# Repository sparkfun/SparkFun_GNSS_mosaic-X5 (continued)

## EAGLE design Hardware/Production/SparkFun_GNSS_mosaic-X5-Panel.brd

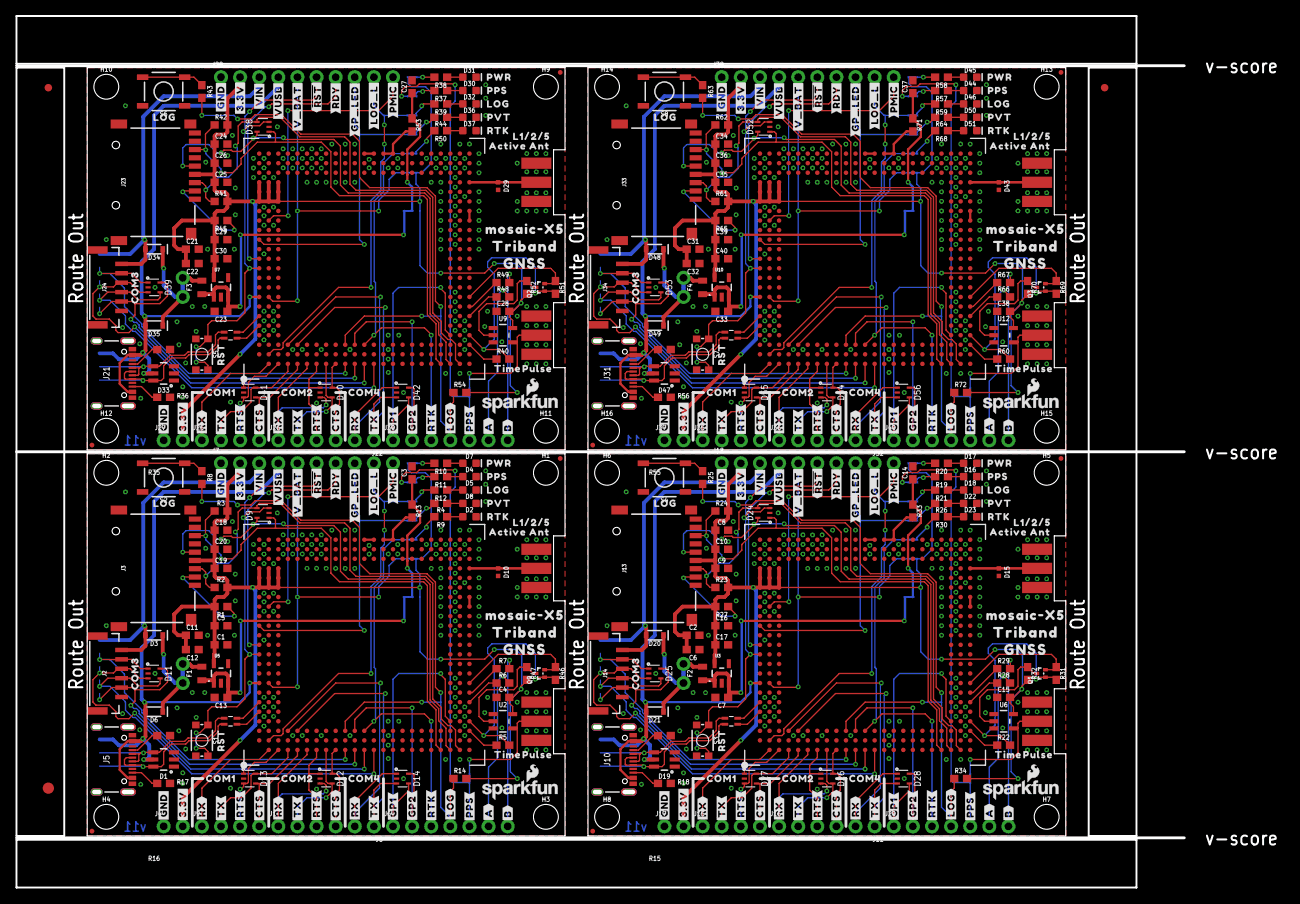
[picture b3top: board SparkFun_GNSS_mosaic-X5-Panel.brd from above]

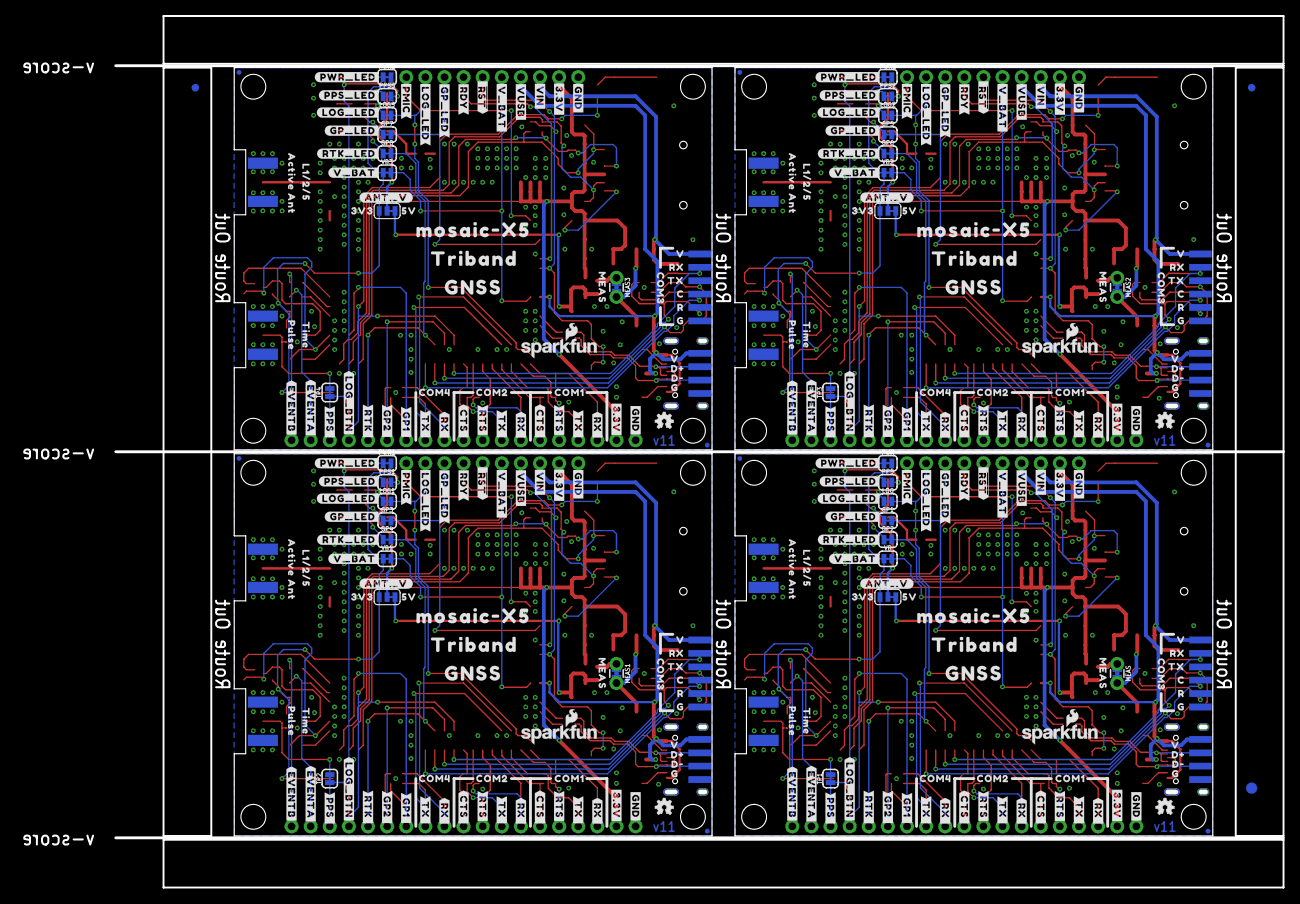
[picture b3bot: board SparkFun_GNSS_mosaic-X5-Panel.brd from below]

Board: 4 copper layers, 155.2 x 115.8 mm, 766 parts (303 on the bottom side), 268 nets.

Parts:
ANT_V, ANT_V1, ANT_V2, ANT_V3: SMT-JUMPER_3_1-NC_TRACE_SILK
C1, C3, C10, C14, C17, C20, C26, C27, C30, C36, C37, C40: 10uF; 0603
C2, C7, C11, C13, C21, C23, C31, C33: 1.0uF; 0603
C4, C6, C9, C12, C15, C19, C22, C25, C28, C32, C35, C38: 0.1uF; 0603
C5, C16, C29, C39: 22uF; 0603
C8, C18, C24, C34: 2.2uF; 0603
D1, D19, D33, D47: ESD Diode; SOT-23-6
D2, D23, D37, D51: WHITE; LED-0603
D3, D6, D20, D21, D34, D35, D48, D49: 3A/10V/280mV; SOD-323
D4, D16, D30, D44: Yellow; LED-0603
D5, D18, D32, D46: GREEN; LED-0603
D7, D17, D31, D45: RED; LED-0603
D8, D22, D36, D50: BLUE; LED-0603
D9, D11, D12, D13, D14, D24, D25, D26, D27, D28, D38, D39, D40, D41, D42, D52, D53, D54, D55, D56: PESDXL4UGUG; SOT353
D10, D15, D29, D43: PESD0402; 0402-TIGHT
E1, E2, E3, E4, E5, E6, E7, E8: SMA; SMA-EDGE
E$1, E$2, E$3, E$4: FIDUCIAL-1X2
E$5, E$6: FIDUCIAL-1.5X3
F1, F2, F3, F4: 6V 0.5A; 0805
GP1, GP2, GP3, GP4, GP5, GP6, GP7, GP8: JUMPER-SMT_2_NC_TRACE_SILK; SMT-JUMPER_2_NC_TRACE_SILK
H1, H2, H3, H4, H5, H6, H7, H8, H9, H10, H11, H12, H13, H14, H15, H16: STAND-OFF
J1, J9, J15, J16, J25, J26, J35, J36: 1X04_NO_SILK
J2, J14, J24, J34: JST-6-SMD-1.25MM-LOCKING
J3, J13, J23, J33: MICROSD; MICROSD-EXTERNALPIN
J4, J8, J11, J17, J22, J27, J32, J37: 1X02_NO_SILK
J5, J10, J21, J31: USB Female Type C Connector; USB-C-16P_4LAYER-PADS
J6, J20, J30, J40: 1X07_NO_SILK
J7, J18, J28, J38: 1X10_NO_SILK
J12, J19, J29, J39: 1X06_SOLDER_PADS
JP1, JP6, JP11, JP16: USB_SOLDER_PADS; USB-SOLDER-PADS
JP2, JP3, JP4, JP5, JP7, JP8, JP9, JP10, JP12, JP13, JP14, JP15, JP21, JP61, JP71, JP81: FIDUCIALUFIDUCIAL; FIDUCIAL-MICRO
LOG, LOG1, LOG2, LOG3: JUMPER-SMT_2_NC_TRACE_SILK; SMT-JUMPER_2_NC_TRACE_SILK
LOGO1, LOGO3, LOGO4, LOGO6, LOGO7, LOGO9, LOGO10, LOGO12: SFE_LOGO_NAME_FLAME10_MM; SFE_LOGO_NAME_FLAME_10MM
LOGO2, LOGO5, LOGO8, LOGO11: OSHW-LOGOMINI; OSHW-LOGO-MINI
MEAS, MEAS1, MEAS2, MEAS3: JUMPER-COMBO_2_NC_TRACE; COMBO-JUMPER_2_NC_TRACE
PPS, PPS1, PPS2, PPS3: JUMPER-SMT_2_NC_TRACE_SILK; SMT-JUMPER_2_NC_TRACE_SILK
PWR, PWR1, PWR2, PWR3: JUMPER-SMT_2_NC_TRACE_SILK; SMT-JUMPER_2_NC_TRACE_SILK
Q1, Q2, Q3, Q9: 20V/0.2A/8MHz/1.2Ω/1Vth; SOT-416FL
R1, R2, R3, R5, R14, R22, R23, R24, R27, R34, R40, R41, R42, R45, R54, R60, R61, R62, R65, R72: 10k; 0603
R4, R11, R19, R26, R31, R32, R37, R44, R46, R47, R51, R52, R57, R64, R69, R70: 2.2k; 0603
R6, R7, R28, R29, R48, R49, R66, R67: 169K; 0603
R8, R9, R10, R20, R25, R30, R38, R43, R50, R58, R63, R68: 1k; 0603
R12, R21, R39, R59: 330; 0603
R13, R33, R53, R71: 0; 0603
R15, R16, R17, R18, R35, R36, R55, R56: 5.1k; 0603
S1, S3, S5, S7: MOMENTARY-SWITCH-SPST-SMD-4.6X2.8MM; TACTILE_SWITCH_SMD_4.6X2.8MM
S2, S4, S6, S8: MOMENTARY-SWITCH-SPST-SMD-5.2-TALL-REDUNDANT; TACTILE_SWITCH_SMD_5.2MM
T1, T2, T3, T4: RFCMF1220100M4T
TP1, TP2, TP3, TP4: JUMPER-SMT_2_NC_TRACE_SILK; SMT-JUMPER_2_NC_TRACE_SILK
U1, U4, U8, U11: MOSAIC-X5X5; MOSAIC_LGA
U2, U6, U9, U12: SN74AHC1G125DBVR; SOT23-5
U3, U5, U7, U10: 3.3V; SOT23-5
U$1, U$193, U$301, U$409: V0
U$2, U$21, U$136, U$164, U$217, U$272, U$325, U$380: TIME0
U$3, U$179, U$287, U$395: GNSS_1
U$4, U$180, U$288, U$396: TRIBAND_2
U$5, U$181, U$289, U$397: MEAS0
U$6, U$47, U$135, U$163, U$220, U$271, U$328, U$379: _ACTIVE_ANT1
U$7, U$195, U$303, U$411: #RTK#0
U$8, U$182, U$290, U$398: C4
U$9, U$183, U$291, U$399: D#2
U$10, U$184, U$292, U$400: D#3
U$11, U$185, U$293, U$401: G0
U$12, U$186, U$294, U$402: R5
U$13, U$48, U$221, U$329: RST0
U$14, U$187, U$295, U$403: RX7
U$15, U$188, U$296, U$404: TX6
U$16, U$189, U$297, U$405: V8
U$17, U$214, U$322, U$430: #EVENTA#0
U$18, U$53, U$82, U$190, U$226, U$298, U$334, U$406: COM30
U$19, U$191, U$299, U$407: MOSAIC#X50
U$20, U$192, U$300, U$408: MOSAIC#X5_0
U$22, U$194, U$302, U$410: G1
U$23, U$196, U$304, U$412: 3V30
U$24, U$197, U$305, U$413: 5V0
U$25, U$32, U$137, U$165, U$218, U$273, U$326, U$381: PULSE1
U$26, U$198, U$306, U$414: #ANT_V#0
U$27, U$199, U$307, U$415: #RTK_LED#0
U$28, U$200, U$308, U$416: RTK0
U$29, U$201, U$309, U$417: PVT0
U$30, U$202, U$310, U$418: #GP1_#0
U$31, U$49, U$222, U$330: LOG0
U$33, U$203, U$311, U$419: #GP2_#0
U$34, U$204, U$312, U$420: #PPS_#0
U$35, U$205, U$313, U$421: #LOG_BTN#0
U$36, U$206, U$314, U$422: #LOG_L#0
U$37, U$207, U$315, U$423: #RDY#0
U$38, U$208, U$316, U$424: #GP_LED#0
U$39, U$209, U$317, U$425: #LOG_LED#0
U$40, U$210, U$318, U$426: #PMIC#0
U$41, U$42, U$211, U$212, U$319, U$320, U$427, U$428: #RTS#0
U$43, U$213, U$321, U$429: #RTK_#0
U$44, U$215, U$323, U$431: #EVENTB#0
U$46, U$69, U$134, U$162, U$219, U$270, U$327, U$378: L1#2#50
U$50, U$79, U$223, U$331: LOG2
U$51, U$80, U$224, U$332: PPS0
U$52, U$81, U$225, U$333: PWR3
U$54, U$83, U$96, U$99, U$227, U$252, U$335, U$360: COM20
U$55, U$84, U$109, U$120, U$228, U$254, U$336, U$362: COM10
U$56, U$85, U$105, U$108, U$229, U$253, U$337, U$361: COM40
U$57, U$63, U$87, U$93, U$110, U$114, U$126, U$128, U$230, U$236, U$255, U$257, U$338, U$344, U$363, U$365: #3#3V#1
U$58, U$68, U$88, U$100, U$231, U$241, U$339, U$349: #CTS#4
U$59, U$65, U$89, U$95, U$113, U$117, U$127, U$129, U$232, U$238, U$256, U$258, U$340, U$346, U$364, U$366: #GND#0
U$60, U$70, U$90, U$101, U$233, U$242, U$341, U$350: #RTS#5
U$61, U$71, U$76, U$91, U$102, U$111, U$234, U$243, U$248, U$342, U$351, U$356: #RX#2
U$62, U$72, U$77, U$92, U$103, U$112, U$235, U$244, U$249, U$343, U$352, U$357: #TX#3
U$64, U$73, U$94, U$104, U$237, U$245, U$345, U$353: #CTS_#4
U$66, U$74, U$78, U$97, U$106, U$115, U$239, U$246, U$250, U$347, U$354, U$358: #RX_#2
U$67, U$75, U$86, U$98, U$107, U$116, U$240, U$247, U$251, U$348, U$355, U$359: #TX_#3
U$118, U$139, U$259, U$367: ##RST##2
U$119, U$148, U$260, U$368: #GP_LED#4
U$121, U$149, U$261, U$369: #PMIC#6
U$122, U$151, U$262, U$370: #RDY#3
U$123, U$130, U$153, U$158, U$263, U$266, U$371, U$374: #VIN#1
U$124, U$131, U$155, U$159, U$264, U$267, U$372, U$375: #VUSB#0
U$125, U$132, U$157, U$160, U$265, U$268, U$373, U$376: #V_BAT#7
U$133, U$161, U$269, U$377: #_#RST##2
U$138, U$166, U$274, U$382: GNSS1
U$140, U$167, U$275, U$383: TRIBAND2
U$141, U$169, U$277, U$385: #LOG_LED#2
U$142, U$170, U$278, U$386: #PPS_LED#1
U$143, U$168, U$276, U$384: #GP_LED#3
U$144, U$171, U$279, U$387: #PWR_LED#0
U$145, U$172, U$280, U$388: #V_BAT#4
U$146, U$173, U$281, U$389: #A#8
U$147, U$174, U$282, U$390: #B#10
U$150, U$175, U$283, U$391: #GP1#0
U$152, U$176, U$284, U$392: #GP2#1
U$154, U$177, U$285, U$393: #LOG#4
U$156, U$178, U$286, U$394: #PPS#6
VB, VB1, VB2, VB3: JUMPER-SMT_2_NC_TRACE_SILK; SMT-JUMPER_2_NC_TRACE_SILK

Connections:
1.8V: Q9.1, R5.2, R46.2, U1.AC4
1.8V1: Q1.1, R22.2, R31.2, U4.AC4
1.8V2: Q2.1, R40.2, R51.2, U8.AC4
1.8V3: Q3.1, R60.2, R69.2, U11.AC4
3.3V: ANT_V.1, C1.1, C4.2, C5.1, C11.1, C12.2, C18.1, C19.1, C20.1, J3.4, J4.2, J7.2, PWR.2, R1.2, R2.2, R3.2, R14.2, R47.2, U1.A18, U1.A19, U1.A20, U1.B18, U1.B19, U1.B20, U1.C18, U1.C19, U1.C20, U2.5, U5.5, VB.1
3.3V1: ANT_V1.1, C2.1, C6.2, C8.1, C9.1, C10.1, C15.2, C16.1, C17.1, J13.4, J17.2, J18.2, PWR1.2, R23.2, R24.2, R27.2, R32.2, R34.2, U3.5, U4.A18, U4.A19, U4.A20, U4.B18, U4.B19, U4.B20, U4.C18, U4.C19, U4.C20, U6.5, VB1.1
3.3V2: ANT_V2.1, C21.1, C22.2, C24.1, C25.1, C26.1, C28.2, C29.1, C30.1, J23.4, J27.2, J28.2, PWR2.2, R41.2, R42.2, R45.2, R52.2, R54.2, U7.5, U8.A18, U8.A19, U8.A20, U8.B18, U8.B19, U8.B20, U8.C18, U8.C19, U8.C20, U9.5, VB2.1
3.3V3: ANT_V3.1, C31.1, C32.2, C34.1, C35.1, C36.1, C38.2, C39.1, C40.1, J33.4, J37.2, J38.2, PWR3.2, R61.2, R62.2, R65.2, R70.2, R72.2, U10.5, U11.A18, U11.A19, U11.A20, U11.B18, U11.B19, U11.B20, U11.C18, U11.C19, U11.C20, U12.5, VB3.1
5V: ANT_V.3, C13.1, F1.1, U5.1, U5.3
5V1: ANT_V1.3, C7.1, F2.1, U3.1, U3.3
5V2: ANT_V2.3, C23.1, F3.1, U7.1, U7.3
5V3: ANT_V3.3, C33.1, F4.1, U10.1, U10.3
!RESET!: D9.3, J7.6, S1.3, S1.4, U1.A11
!RESET!1: D24.3, J18.6, S3.3, S3.4, U4.A11
!RESET!2: D38.3, J28.6, S5.3, S5.4, U8.A11
!RESET!3: D52.3, J38.6, S7.3, S7.4, U11.A11
ANT_V: ANT_V.2, C3.1, R13.1
ANT_V1: ANT_V1.2, C14.1, R33.1
ANT_V2: ANT_V2.2, C27.1, R53.1
ANT_V3: ANT_V3.2, C37.1, R71.1
CC1: J5.A5, R17.2
CC2: J5.B5, R16.2
CC3: J10.A5, R18.2
CC4: J10.B5, R15.2
CC5: J21.A5, R36.2
CC6: J21.B5, R35.2
CC7: J31.A5, R56.2
CC8: J31.B5, R55.2
COM1_CTS: D13.4, J9.4, U1.E1
COM1_CTS1: D27.4, J15.4, U4.E1
COM1_CTS2: D41.4, J25.4, U8.E1
COM1_CTS3: D55.4, J35.4, U11.E1
COM1_RTS: D13.3, J9.3, U1.C1
COM1_RTS1: D27.3, J15.3, U4.C1
COM1_RTS2: D41.3, J25.3, U8.C1
COM1_RTS3: D55.3, J35.3, U11.C1
COM1_RX: D13.1, J9.1, U1.B1
COM1_RX1: D27.1, J15.1, U4.B1
COM1_RX2: D41.1, J25.1, U8.B1
COM1_RX3: D55.1, J35.1, U11.B1
COM1_TX: D13.5, J9.2, U1.D1
COM1_TX1: D27.5, J15.2, U4.D1
COM1_TX2: D41.5, J25.2, U8.D1
COM1_TX3: D55.5, J35.2, U11.D1
COM2_CTS: D12.5, J1.4, U1.J1
COM2_CTS1: D26.5, J16.4, U4.J1
COM2_CTS2: D40.5, J26.4, U8.J1
COM2_CTS3: D54.5, J36.4, U11.J1
COM2_RTS: D12.1, J1.3, U1.G1
COM2_RTS1: D26.1, J16.3, U4.G1
COM2_RTS2: D40.1, J26.3, U8.G1
COM2_RTS3: D54.1, J36.3, U11.G1
COM2_RX: D12.3, J1.1, U1.F1
COM2_RX1: D26.3, J16.1, U4.F1
COM2_RX2: D40.3, J26.1, U8.F1
COM2_RX3: D54.3, J36.1, U11.F1
COM2_TX: D12.4, J1.2, U1.H1
COM2_TX1: D26.4, J16.2, U4.H1
COM2_TX2: D40.4, J26.2, U8.H1
COM2_TX3: D54.4, J36.2, U11.H1
COM3_CTS: D11.4, J2.4, J12.4, U1.N1
COM3_CTS1: D25.4, J14.4, J19.4, U4.N1
COM3_CTS2: D39.4, J24.4, J29.4, U8.N1
COM3_CTS3: D53.4, J34.4, J39.4, U11.N1
COM3_RTS: D11.5, J2.5, J12.5, U1.L1
COM3_RTS1: D25.5, J14.5, J19.5, U4.L1
COM3_RTS2: D39.5, J24.5, J29.5, U8.L1
COM3_RTS3: D53.5, J34.5, J39.5, U11.L1
COM3_RX: D11.1, J2.2, J12.2, U1.K1
COM3_RX1: D25.1, J14.2, J19.2, U4.K1
COM3_RX2: D39.1, J24.2, J29.2, U8.K1
COM3_RX3: D53.1, J34.2, J39.2, U11.K1
COM3_TX: D11.3, J2.3, J12.3, U1.M1
COM3_TX1: D25.3, J14.3, J19.3, U4.M1
COM3_TX2: D39.3, J24.3, J29.3, U8.M1
COM3_TX3: D53.3, J34.3, J39.3, U11.M1
COM4_RX: D14.1, J8.2, U1.D3
COM4_RX1: D28.1, J11.2, U4.D3
COM4_RX2: D42.1, J22.2, U8.D3
COM4_RX3: D56.1, J32.2, U11.D3
COM4_TX: D14.3, J8.1, U1.E3
COM4_TX1: D28.3, J11.1, U4.E3
COM4_TX2: D42.3, J22.1, U8.E3
COM4_TX3: D56.3, J32.1, U11.E3
D+: T1.B2, U1.A5
D+1: T2.B2, U4.A5
D+2: T3.B2, U8.A5
D+3: T4.B2, U11.A5
D-: T1.A2, U1.A6
D-1: T2.A2, U4.A6
D-2: T3.A2, U8.A6
D-3: T4.A2, U11.A6
EVENTA: J6.6, R6.2
EVENTA1: J20.6, R28.2
EVENTA2: J30.6, R48.2
EVENTA3: J40.6, R66.2
EVENTB: J6.7, R7.2
EVENTB1: J20.7, R29.2
EVENTB2: J30.7, R49.2
EVENTB3: J40.7, R67.2
GND: C1.2, C3.2, C4.1, C5.2, C11.2, C12.1, C13.2, C18.2, C19.2, C20.2, D1.2, D2.C, D4.C, D5.C, D7.C, D8.C, D9.2, D10.2, D11.2, D12.2, D13.2, D14.2, E1.GND@0, E1.GND@1, E1.GND@2, E1.GND@3, E2.GND@0, E2.GND@1, E2.GND@2, E2.GND@3, J2.6, J3.6, J3.10, J3.11, J3.12, J3.13, J4.1, J5.GND, J5.GND2, J7.1, J12.6, JP1.GND, R16.1, R17.1, S1.1, S1.2, S2.1, S2.2, U1.A3, U1.A4, U1.A7, U1.A15, U1.A16, U1.A17, U1.A21, U1.A22, U1.A23, U1.AA13, U1.AA14, U1.AA15, U1.AA16, U1.AA17, U1.AA18, U1.AA19, U1.AA20, U1.AA21, U1.AA22, U1.AA23, U1.AB2, U1.AB3, U1.AB4, U1.AB5, U1.AB6, U1.AB7, U1.AB8, U1.AB13, U1.AB14, U1.AB15, U1.AB16, U1.AB17, U1.AB18, U1.AB19, U1.AB20, U1.AB21, U1.AB22, U1.AB23, U1.AC13, U1.AC15, U1.AC18, U1.AC19, U1.AC21, U1.AC22, U1.AC23, U1.B4, U1.B5, U1.B6, U1.B7, U1.B13, U1.B17, U1.B21, U1.C4, U1.C7, U1.C15, U1.C16, U1.C17, U1.C23, U1.D2, U1.D21, U1.D22, U1.D23, U1.E2, U1.E21, U1.E22, U1.E23, U1.F21, U1.F22, U1.F23, U1.G2, U1.G21, U1.G23, U1.H21, U1.H22, U1.H23, U1.J21, U1.J22, U1.J23, U1.K2, U1.K21, U1.K22, U1.K23, U1.L21, U1.L22, U1.L23, U1.M21, U1.M22, U1.N21, U1.N22, U1.P1, U1.P2, U1.P3, U1.P21, U1.P22, U1.R3, U1.R21, U1.R22, U1.T21, U1.T22, U1.T23, U1.U2, U1.U21, U1.U22, U1.U23, U1.V21, U1.V22, U1.V23, U1.W21, U1.W22, U1.W23, U1.Y2, U1.Y21, U1.Y22, U1.Y23, U2.1, U2.3, U5.2
GND1: C2.2, C6.1, C7.2, C8.2, C9.2, C10.2, C14.2, C15.1, C16.2, C17.2, D15.2, D16.C, D17.C, D18.C, D19.2, D22.C, D23.C, D24.2, D25.2, D26.2, D27.2, D28.2, E3.GND@0, E3.GND@1, E3.GND@2, E3.GND@3, E4.GND@0, E4.GND@1, E4.GND@2, E4.GND@3, J10.GND, J10.GND2, J13.6, J13.10, J13.11, J13.12, J13.13, J14.6, J17.1, J18.1, J19.6, JP6.GND, R15.1, R18.1, S3.1, S3.2, S4.1, S4.2, U3.2, U4.A3, U4.A4, U4.A7, U4.A15, U4.A16, U4.A17, U4.A21, U4.A22, U4.A23, U4.AA13, U4.AA14, U4.AA15, U4.AA16, U4.AA17, U4.AA18, U4.AA19, U4.AA20, U4.AA21, U4.AA22, U4.AA23, U4.AB2, U4.AB3, U4.AB4, U4.AB5, U4.AB6, U4.AB7, U4.AB8, U4.AB13, U4.AB14, U4.AB15, U4.AB16, U4.AB17, U4.AB18, U4.AB19, U4.AB20, U4.AB21, U4.AB22, U4.AB23, U4.AC13, U4.AC15, U4.AC18, U4.AC19, U4.AC21, U4.AC22, U4.AC23, U4.B4, U4.B5, U4.B6, U4.B7, U4.B13, U4.B17, U4.B21, U4.C4, U4.C7, U4.C15, U4.C16, U4.C17, U4.C23, U4.D2, U4.D21, U4.D22, U4.D23, U4.E2, U4.E21, U4.E22, U4.E23, U4.F21, U4.F22, U4.F23, U4.G2, U4.G21, U4.G23, U4.H21, U4.H22, U4.H23, U4.J21, U4.J22, U4.J23, U4.K2, U4.K21, U4.K22, U4.K23, U4.L21, U4.L22, U4.L23, U4.M21, U4.M22, U4.N21, U4.N22, U4.P1, U4.P2, U4.P3, U4.P21, U4.P22, U4.R3, U4.R21, U4.R22, U4.T21, U4.T22, U4.T23, U4.U2, U4.U21, U4.U22, U4.U23, U4.V21, U4.V22, U4.V23, U4.W21, U4.W22, U4.W23, U4.Y2, U4.Y21, U4.Y22, U4.Y23, U6.1, U6.3
GND2: C21.2, C22.1, C23.2, C24.2, C25.2, C26.2, C27.2, C28.1, C29.2, C30.2, D29.2, D30.C, D31.C, D32.C, D33.2, D36.C, D37.C, D38.2, D39.2, D40.2, D41.2, D42.2, E5.GND@0, E5.GND@1, E5.GND@2, E5.GND@3, E6.GND@0, E6.GND@1, E6.GND@2, E6.GND@3, J21.GND, J21.GND2, J23.6, J23.10, J23.11, J23.12, J23.13, J24.6, J27.1, J28.1, J29.6, JP11.GND, R35.1, R36.1, S5.1, S5.2, S6.1, S6.2, U7.2, U8.A3, U8.A4, U8.A7, U8.A15, U8.A16, U8.A17, U8.A21, U8.A22, U8.A23, U8.AA13, U8.AA14, U8.AA15, U8.AA16, U8.AA17, U8.AA18, U8.AA19, U8.AA20, U8.AA21, U8.AA22, U8.AA23, U8.AB2, U8.AB3, U8.AB4, U8.AB5, U8.AB6, U8.AB7, U8.AB8, U8.AB13, U8.AB14, U8.AB15, U8.AB16, U8.AB17, U8.AB18, U8.AB19, U8.AB20, U8.AB21, U8.AB22, U8.AB23, U8.AC13, U8.AC15, U8.AC18, U8.AC19, U8.AC21, U8.AC22, U8.AC23, U8.B4, U8.B5, U8.B6, U8.B7, U8.B13, U8.B17, U8.B21, U8.C4, U8.C7, U8.C15, U8.C16, U8.C17, U8.C23, U8.D2, U8.D21, U8.D22, U8.D23, U8.E2, U8.E21, U8.E22, U8.E23, U8.F21, U8.F22, U8.F23, U8.G2, U8.G21, U8.G23, U8.H21, U8.H22, U8.H23, U8.J21, U8.J22, U8.J23, U8.K2, U8.K21, U8.K22, U8.K23, U8.L21, U8.L22, U8.L23, U8.M21, U8.M22, U8.N21, U8.N22, U8.P1, U8.P2, U8.P3, U8.P21, U8.P22, U8.R3, U8.R21, U8.R22, U8.T21, U8.T22, U8.T23, U8.U2, U8.U21, U8.U22, U8.U23, U8.V21, U8.V22, U8.V23, U8.W21, U8.W22, U8.W23, U8.Y2, U8.Y21, U8.Y22, U8.Y23, U9.1, U9.3
GND3: C31.2, C32.1, C33.2, C34.2, C35.2, C36.2, C37.2, C38.1, C39.2, C40.2, D43.2, D44.C, D45.C, D46.C, D47.2, D50.C, D51.C, D52.2, D53.2, D54.2, D55.2, D56.2, E7.GND@0, E7.GND@1, E7.GND@2, E7.GND@3, E8.GND@0, E8.GND@1, E8.GND@2, E8.GND@3, J31.GND, J31.GND2, J33.6, J33.10, J33.11, J33.12, J33.13, J34.6, J37.1, J38.1, J39.6, JP16.GND, R55.1, R56.1, S7.1, S7.2, S8.1, S8.2, U10.2, U11.A3, U11.A4, U11.A7, U11.A15, U11.A16, U11.A17, U11.A21, U11.A22, U11.A23, U11.AA13, U11.AA14, U11.AA15, U11.AA16, U11.AA17, U11.AA18, U11.AA19, U11.AA20, U11.AA21, U11.AA22, U11.AA23, U11.AB2, U11.AB3, U11.AB4, U11.AB5, U11.AB6, U11.AB7, U11.AB8, U11.AB13, U11.AB14, U11.AB15, U11.AB16, U11.AB17, U11.AB18, U11.AB19, U11.AB20, U11.AB21, U11.AB22, U11.AB23, U11.AC13, U11.AC15, U11.AC18, U11.AC19, U11.AC21, U11.AC22, U11.AC23, U11.B4, U11.B5, U11.B6, U11.B7, U11.B13, U11.B17, U11.B21, U11.C4, U11.C7, U11.C15, U11.C16, U11.C17, U11.C23, U11.D2, U11.D21, U11.D22, U11.D23, U11.E2, U11.E21, U11.E22, U11.E23, U11.F21, U11.F22, U11.F23, U11.G2, U11.G21, U11.G23, U11.H21, U11.H22, U11.H23, U11.J21, U11.J22, U11.J23, U11.K2, U11.K21, U11.K22, U11.K23, U11.L21, U11.L22, U11.L23, U11.M21, U11.M22, U11.N21, U11.N22, U11.P1, U11.P2, U11.P3, U11.P21, U11.P22, U11.R3, U11.R21, U11.R22, U11.T21, U11.T22, U11.T23, U11.U2, U11.U21, U11.U22, U11.U23, U11.V21, U11.V22, U11.V23, U11.W21, U11.W22, U11.W23, U11.Y2, U11.Y21, U11.Y22, U11.Y23, U12.1, U12.3
GP1: D14.4, J6.1, U1.AA4
GP2: D14.5, J6.2, U1.L3
GP3: D28.4, J20.1, U4.AA4
GP4: D28.5, J20.2, U4.L3
GP5: D42.4, J30.1, U8.AA4
GP6: D42.5, J30.2, U8.L3
GP7: D56.4, J40.1, U11.AA4
GP8: D56.5, J40.2, U11.L3
GPS_ANT1: D10.1, E1.SIG, U1.AC20
GPS_ANT2: D15.1, E3.SIG, U4.AC20
GPS_ANT3: D29.1, E5.SIG, U8.AC20
GPS_ANT4: D43.1, E7.SIG, U11.AC20
LOG_BTN: J6.4, R8.2, R14.1, U1.K3
LOG_BTN1: J20.4, R25.2, R34.1, U4.K3
LOG_BTN2: J30.4, R43.2, R54.1, U8.K3
LOG_BTN3: J40.4, R63.2, R72.1, U11.K3
LOG_LED: J7.9, LOG.2, U1.B2
LOG_LED1: J18.9, LOG1.2, U4.B2
LOG_LED2: J28.9, LOG2.2, U8.B2
LOG_LED3: J38.9, LOG3.2, U11.B2
MEAS: D3.C, D6.C, MEAS.2, MEAS.4
MEAS1: D20.C, D21.C, MEAS1.2, MEAS1.4
MEAS2: D34.C, D35.C, MEAS2.2, MEAS2.4
MEAS3: D48.C, D49.C, MEAS3.2, MEAS3.4
MODULE_RDY: J7.7, U1.A12
MODULE_RDY1: J18.7, U4.A12
MODULE_RDY2: J28.7, U8.A12
MODULE_RDY3: J38.7, U11.A12
unnamed: R8.1, S2.3, S2.4
unnamed: D4.A, R11.1
unnamed: PPS.1, R11.2
unnamed: F1.2, MEAS.1, MEAS.3
unnamed: J3.2, R1.1
unnamed: R6.1, U1.AC6
unnamed: R7.1, U1.AC7
unnamed: D2.A, R9.1
unnamed: GP2.1, R9.2
unnamed: U1.AC16, U1.AC17
unnamed: D8.A, R4.1
unnamed: GP1.1, R4.2
unnamed: D16.A, R19.1
unnamed: D7.A, R10.1
unnamed: U1.M23, U1.N23
unnamed: D5.A, R12.1
unnamed: LOG.1, R12.2
unnamed: PPS1.1, R19.2
unnamed: D17.A, R20.1
unnamed: PWR.1, R10.2
unnamed: D18.A, R21.1
unnamed: LOG1.1, R21.2
unnamed: PWR1.1, R20.2
unnamed: U4.AC16, U4.AC17
unnamed: U4.M23, U4.N23
unnamed: R5.1, U1.AC3
unnamed: R22.1, U4.AC3
unnamed: R25.1, S4.3, S4.4
unnamed: D22.A, R26.1
unnamed: GP3.1, R26.2
unnamed: F2.2, MEAS1.1, MEAS1.3
unnamed: J13.2, R27.1
unnamed: R28.1, U4.AC6
unnamed: R29.1, U4.AC7
unnamed: D23.A, R30.1
unnamed: GP4.1, R30.2
unnamed: D30.A, R37.1
unnamed: PPS2.1, R37.2
unnamed: D31.A, R38.1
unnamed: D32.A, R39.1
unnamed: LOG2.1, R39.2
unnamed: PWR2.1, R38.2
unnamed: U8.AC16, U8.AC17
unnamed: U8.M23, U8.N23
unnamed: R40.1, U8.AC3
unnamed: R43.1, S6.3, S6.4
unnamed: D36.A, R44.1
unnamed: GP5.1, R44.2
unnamed: F3.2, MEAS2.1, MEAS2.3
unnamed: J23.2, R45.1
unnamed: R48.1, U8.AC6
unnamed: R49.1, U8.AC7
unnamed: D37.A, R50.1
unnamed: GP6.1, R50.2
unnamed: D44.A, R57.1
unnamed: PPS3.1, R57.2
unnamed: D45.A, R58.1
unnamed: D46.A, R59.1
unnamed: LOG3.1, R59.2
unnamed: PWR3.1, R58.2
unnamed: U11.AC16, U11.AC17
unnamed: U11.M23, U11.N23
unnamed: R60.1, U11.AC3
unnamed: R63.1, S8.3, S8.4
unnamed: D50.A, R64.1
unnamed: GP7.1, R64.2
unnamed: F4.2, MEAS3.1, MEAS3.3
unnamed: J33.2, R65.1
unnamed: R66.1, U11.AC6
unnamed: R67.1, U11.AC7
unnamed: D51.A, R68.1
unnamed: GP8.1, R68.2
PMIC_ON_REQ: J7.10, U1.B16
PMIC_ON_REQ1: J18.10, U4.B16
PMIC_ON_REQ2: J28.10, U8.B16
PMIC_ON_REQ3: J38.10, U11.B16
PPS: E2.SIG, TP1.2, U2.4
PPS1: E4.SIG, TP2.2, U6.4
PPS2: E6.SIG, TP3.2, U9.4
PPS3: E8.SIG, TP4.2, U12.4
PPS_1: Q1.3, R32.1, U6.2
PPS_1V1: Q1.2, R31.1, U4.AC8
PPS_1V2: Q2.2, R51.1, U8.AC8
PPS_1V3: Q3.2, R69.1, U11.AC8
PPS_1V8: Q9.2, R46.1, U1.AC8
PPS_2: Q2.3, R52.1, U9.2
PPS_3: Q9.3, R47.1, U2.2
PPS_3V1: J20.5, PPS1.2, TP2.1
PPS_3V2: J30.5, PPS2.2, TP3.1
PPS_3V3: J6.5, PPS.2, TP1.1
PPS_3V4: J40.5, PPS3.2, TP4.1
PPS_4: Q3.3, R70.1, U12.2
PVT_LED: GP1.2, J7.8, U1.A14
PVT_LED1: GP3.2, J18.8, U4.A14
PVT_LED2: GP5.2, J28.8, U8.A14
PVT_LED3: GP7.2, J38.8, U11.A14
RTK_LED: GP2.2, J6.3, U1.M3
RTK_LED1: GP4.2, J20.3, U4.M3
RTK_LED2: GP6.2, J30.3, U8.M3
RTK_LED3: GP8.2, J40.3, U11.M3
SD_CLK: D9.5, J3.5, U1.AA1
SD_CLK1: D24.5, J13.5, U4.AA1
SD_CLK2: D38.5, J23.5, U8.AA1
SD_CLK3: D52.5, J33.5, U11.AA1
SD_CMD: D9.4, J3.3, R2.1, U1.AB1
SD_CMD1: D24.4, J13.3, R23.1, U4.AB1
SD_CMD2: D38.4, J23.3, R41.1, U8.AB1
SD_CMD3: D52.4, J33.3, R61.1, U11.AB1
SD_DATA: D9.1, J3.7, R3.1, U1.Y1
SD_DATA1: D24.1, J13.7, R24.1, U4.Y1
SD_DATA2: D38.1, J23.7, R42.1, U8.Y1
SD_DATA3: D52.1, J33.7, R62.1, U11.Y1
USB_D+: D1.6, J5.A6, J5.B6, JP1.D+, T1.B1
USB_D+1: D19.6, J10.A6, J10.B6, JP6.D+, T2.B1
USB_D+2: D33.6, J21.A6, J21.B6, JP11.D+, T3.B1
USB_D+3: D47.6, J31.A6, J31.B6, JP16.D+, T4.B1
USB_D-: D1.4, J5.A7, J5.B7, JP1.D-, T1.A1
USB_D-1: D19.4, J10.A7, J10.B7, JP6.D-, T2.A1
USB_D-2: D33.4, J21.A7, J21.B7, JP11.D-, T3.A1
USB_D-3: D47.4, J31.A7, J31.B7, JP16.D-, T4.A1
VANT: R13.2, U1.P23, U1.R23
VANT1: R33.2, U4.P23, U4.R23
VANT2: R53.2, U8.P23, U8.R23
VANT3: R71.2, U11.P23, U11.R23
VIN: D3.A, J2.1, J7.3, J12.1
VIN1: D20.A, J14.1, J18.3, J19.1
VIN2: D34.A, J24.1, J28.3, J29.1
VIN3: D48.A, J34.1, J38.3, J39.1
V_BAT: J7.5, U1.B8, VB.2
V_BAT1: J18.5, U4.B8, VB1.2
V_BAT2: J28.5, U8.B8, VB2.2
V_BAT3: J38.5, U11.B8, VB3.2
V_USB: D1.5, D6.A, J5.VBUS1, J5.VBUS2, J7.4, JP1.VBUS, U1.A8
V_USB1: D19.5, D21.A, J10.VBUS1, J10.VBUS2, J18.4, JP6.VBUS, U4.A8
V_USB2: D33.5, D35.A, J21.VBUS1, J21.VBUS2, J28.4, JP11.VBUS, U8.A8
V_USB3: D47.5, D49.A, J31.VBUS1, J31.VBUS2, J38.4, JP16.VBUS, U11.A8

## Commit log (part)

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2023-07-14 Add Mosaic-X5 Via-In-Pad
2023-07-17 Add GP_LED2 (added in v1.6.0 of the datasheet)
2023-07-17 Add KSZ8041NL Ethernet Phy
2023-07-17 Route board.
2023-07-19 Rename lib. Increase tStop/tCream.
2023-07-19 Add jumper to ant voltage. Add production panel.
2023-07-19 Add production files.
2023-07-19 Add partID
2023-07-20 Rename lib - correct typo
2023-07-20 Move tDocu circle to A1
2023-07-20 Remove tStop and tCream from A1
2023-07-20 Correct_Ethernet_PHY_Pads
2023-07-24 Add Ethernet PHY PROD_ID
2023-07-26 Fixed tCream on mosaic pin 1.
2023-07-26 Adding production files
2023-07-27 Add ESD and USB choke.
2023-07-27 Add prod_IDs
2023-08-23 Fix 1.8V net, fix silk, add more ESD protection, add LOG pullup.
2023-08-23 Add v11 panel.
2023-08-23 Swap CTS/RTS on COM3 JST connector.
2023-08-23 Update panel files with CTS/RTS
2023-08-23 Update board measurements.
2023-10-03 Add DNP text to SD ESD
2023-10-10 Update Template Files
    Updated README, CONTRIBUTING, ISSUES_TEMPLATE, and LICENSE files
2023-10-10 Change ESD diode on microSD interface.
2023-10-12 Update product photo
    Update to new photo
2023-10-14 Initial Commit
    Excluding RxTools and PP-SDK info/files
2023-10-16 Update README.md
    update link
2023-10-17 Update print_view.md
    Add in software sections
2023-10-19 Update QR codes
2023-10-19 Update README.md
    Adjust image size
    Update directory information
2023-11-10 L5 Configuration
    Includes instructions for enabling the L5 frequency band
2024-01-04 Add thumbnail
2024-01-04 Fix image link
    Product image was replaced
2024-01-04 Deployed 71825b2 with MkDocs version: 1.5.3
2024-01-29 Update mkdocs.yml
    Add google analytics
2024-02-06 Update LICENSE.md
    Fix carriage returns
2024-02-06 Content tab styling
    Update content tab styling
    - Accent color on mouse hover
    - Outline on tabs and adds background color to inactive tabs
2024-02-06 Update LICENSE.md
    Remove carriage returns
2024-02-06 Add image optimization
    Update workflow for required plugins and tools
    Add optimize plugin to mkdocs.yml
2024-02-12 Update README.md
    Move Documentation section higher (mimic RTK mosaic-X5)
    Add badges for MkDocs Material and build
2024-02-12 Update troubleshooting_tips.md
    Add data logging info
2024-02-12 Update resources.md
    Fix video link
2024-02-12 Update hardware_overview.md
    Fix links to content tabs
2024-02-12 Fix grammar
2024-02-12 Update introduction.md
    Add RTK tutorial
    Add RTK Surveying blog post
2024-02-12 Update hardware_overview.md
    Reduce image size in tooltip
    Add info on setting up data stream to SD card
2024-02-12 Update extra.css
    Fix content tab aesthetic for titles including:
    - code blocks
    - keyboard buttons
2024-03-06 Add RTK mosaic-X5
    Include the RTK mosaic-X5 hookup guide
    Add the RTK mosaic-X5 to the comparison table
2024-03-06 Update introduction.md
    Replace soldering station (retired)
    Fix typo
2024-03-08 Deployed 3b8d47f with MkDocs version: 1.5.3
2024-05-17 Remove CSS
    Removes instances of col-# classes
2024-05-17 Update video CSS
    Adds new CSS classes for video containers
    Updates implementation in the hookup guide
2024-05-17 Update resources.md
    Add jammer fest blog post
2024-05-17 Update mkdocs.yml
    Add instant preview
2024-05-17 Update video CSS
    Update video container implementation
    - Removes video_cards class
2024-05-17 Remove Pixhawk
    Pixhawk 4 was discontinued by the manufacturer
2024-05-17 Update extra.css
    Remove permalink styling
    Remove stylings for old pdf generation
2024-06-01 Rename file
2024-06-01 Update ESD Admonition
    Adds link to anti-static wrist trap
2024-06-01 Update favicon
    Renames file to sfe-logo.png
    Adds favicon.ico
    Removes redundant file
2024-06-01 Deployed 0e375b9 with MkDocs version: 1.6.0
2025-02-20 Update introduction.md
    Fixing missing image
2025-02-20 Update introduction.md
    Fixed another missing image
2025-02-20 Deployed c387cc3 with MkDocs version: 1.6.1
2025-09-10 Replace <center> tags
    Updated all documentation files to use <article style="text-align: center;" markdown> in place of deprecated <center> tags for centering content. This improves HTML5 compliance and ensures consistent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
2025-09-10 Update copyright year to 2025
    Changed the copyright year from 2023 to 2025 in LICENSE.md and mkdocs.yml to reflect the current year.
2025-09-10 Update documentation build workflow
    Disable plugins on local builds
    Remove the git-authors plugin
2025-09-10 Replace sfe-logo icon with sfe and update references
    Replaces the 'sfe-logo' SVG icon with a new 'sfe.svg' file and updates all references in mkdocs.yml to use 'sfe' instead of 'sfe-logo'. Also clarifies a comment in the theme configuration.
2025-09-10 Add branding SVG icons
    Added multiple SVG logo files for various brands (Arduino, Espressif, Fugro, Hexagon, KiCad, Python, Quectel, Raspberry Pi, Septentrio, SiTime, SparkFun, u-blox)
2025-09-10 Add custom JS, partials, and update MkDocs config
    Added new JavaScript files for 3D color adjustment and KaTeX support, along with a README for the scripts directory. Introduced new partials for copyright, generator, and social links. Updated mkdocs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
2025-09-10 Update icon references
2025-09-10 Deployed 30419c5 with MkDocs version: 1.6.1
2025-09-10 Add product comparison
2025-09-10 Deployed b342ac7 with MkDocs version: 1.6.1
2025-09-12 Update component documentation
    Updates the firmware, datasheet, and manuals for the mosaic-X5
2025-09-15 Deployed 0c968c1 with MkDocs version: 1.6.1
2025-09-15 Update web_interface.md
    Fix typo
2025-09-15 Deployed 7daa220 with MkDocs version: 1.6.1
2025-09-15 Replace <sup> tag
    Replace <sup> tag with markdown notation
2025-09-18 Add note for USB silkscreen
    A notice for an error on the silkscreen on the test pads of the USB interface
2025-09-18 Update <article> tags for videos
    Consolidates redundant <article> tags used on the video class, which were replacements from the update for the <center> tags
    Adds the "margin: auto;" attribute to the element's style for centering the video
2025-09-18 Update extra.css
    Sets the width of the QR code images that are rendered for better conformity, when printing out the document
2025-09-18 Deployed 233518f with MkDocs version: 1.6.1
2025-09-18 Remove submodule process
    Remove submodule retrieval from workflow
2026-05-28 Remove "Made in the USA" silk - for foreign PCB manufacture
